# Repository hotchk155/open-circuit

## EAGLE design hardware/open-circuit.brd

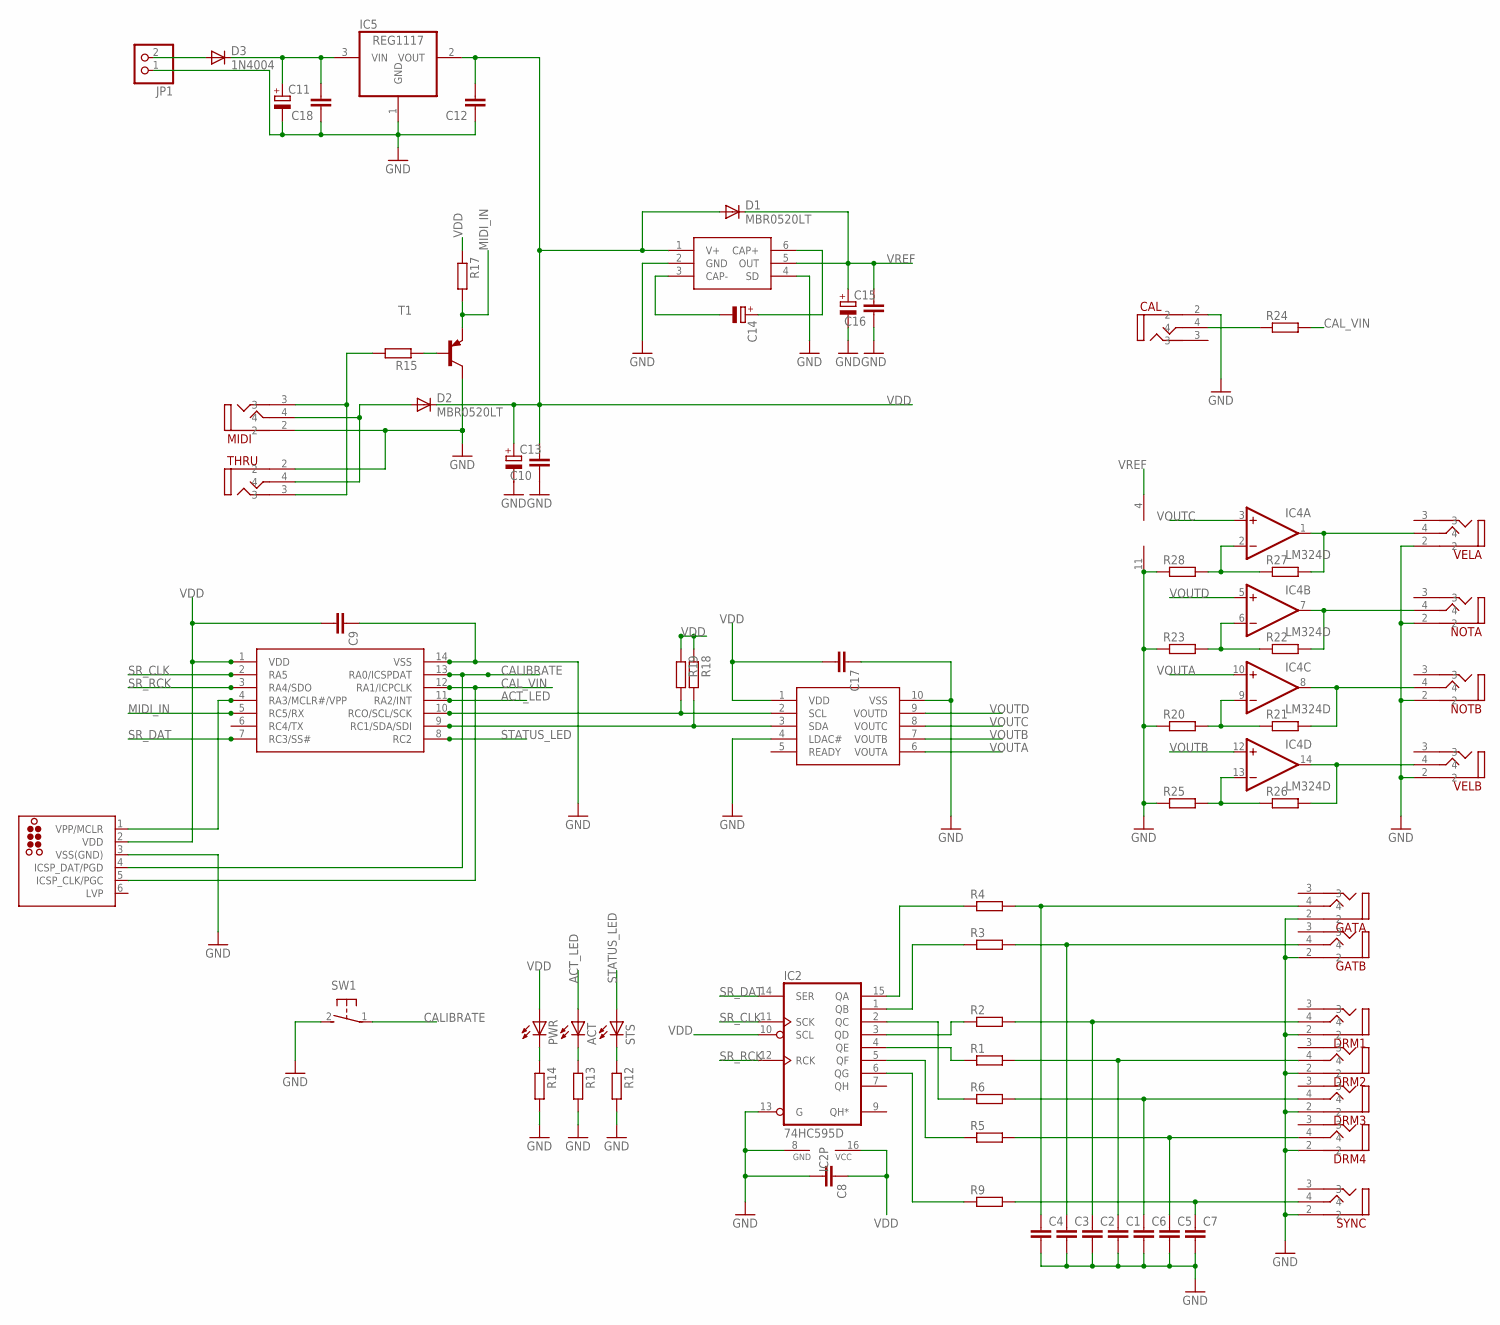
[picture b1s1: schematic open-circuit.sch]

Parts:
ACT: LED3MM
C1, C2, C3, C4, C5, C6, C7, C8, C9, C10, C12, C16, C17, C18: C-EUC0805; C0805
C11: CPOL-EUE2.5-5; E2,5-5
C13, C14, C15: CPOL-EUSMCA; SMC_A
CAL: VERTICAL_3_5MM_SOCKET
D1, D2: MBR0520LT; SOD123
D3: 1N4004; DO-VERT
DRM1, DRM2, DRM3, DRM4: VERTICAL_3_5MM_SOCKET
GATA: VERTICAL_3_5MM_SOCKET
GATB: VERTICAL_3_5MM_SOCKET
IC1: PIC16F1825SO14; SO14
IC2: 74HC595D; SO16
IC3: MCP4728_QUAD_DAC; MSOP10
IC4: LM324D; SO14
IC5: REG1117; SOT223
IC6: LM27675M5_CHARGEPUMP; SOT23-6
ISCP: TC2030-MCP-NL
JP1: PINHD-1X2; 1X02
MIDI: VERTICAL_3_5MM_SOCKET
NOTA: VERTICAL_3_5MM_SOCKET
NOTB: VERTICAL_3_5MM_SOCKET
PWR: LED3MM
R1, R2, R3, R4, R5, R6, R9, R12, R13, R14, R15, R17, R18, R19, R20, R21, R22, R23, R24, R25, R26, R27, R28: R-EU_R0805; R0805
STS: LED3MM
SW1: 31-XX; B3F-31XX
SYNC: VERTICAL_3_5MM_SOCKET
T1: MMBT3906LT1-PNP-SOT23-BEC; SOT23-BEC
THRU: VERTICAL_3_5MM_SOCKET
VELA: VERTICAL_3_5MM_SOCKET
VELB: VERTICAL_3_5MM_SOCKET

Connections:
ACT_LED: ACT.A, IC1.11 (RA2/INT)
CALIBRATE: IC1.13 (RA0/ICSPDAT), ISCP.4 (ICSP_DAT/PGD), SW1.1
CAL_VIN: IC1.12 (RA1/ICPCLK), ISCP.5 (ICSP_CLK/PGC), R24.2
GND: C1.2, C2.2, C3.2, C4.2, C5.2, C6.2, C7.2, C8.2, C9.1, C10.1, C11.-, C12.1, C13.-, C15.-, C16.1, C17.1, C18.1, CAL.2, DRM1.2, DRM2.2, DRM3.2, DRM4.2, GATA.2, GATB.2, IC1.14 (VSS), IC2.8 (GND), IC2.13 (G), IC3.4 (LDAC#), IC3.10 (VSS), IC4.11 (V-), IC5.1 (GND), IC6.2 (GND), IC6.4 (SD), ISCP.3 (VSS(GND)), JP1.1, MIDI.2, NOTA.2, NOTB.2, R12.2, R13.2, R14.2, R20.1, R23.1, R25.1, R28.1, SW1.2 (S), SYNC.2, T1.C, THRU.2, VELA.2, VELB.2
MIDI_IN: IC1.5 (RC5/RX), R17.2, T1.E
unnamed: C4.1, GATA.4, R4.2
unnamed: IC4.1 (OUT), R27.2, VELA.4
unnamed: IC4.7 (OUT), NOTA.4, R22.2
unnamed: IC4.8 (OUT), NOTB.4, R21.2
unnamed: IC4.14 (OUT), R26.2, VELB.4
unnamed: C3.1, GATB.4, R3.2
unnamed: C2.1, DRM1.4, R2.2
unnamed: C1.1, DRM2.4, R1.2
unnamed: C6.1, DRM3.4, R6.2
unnamed: C5.1, DRM4.4, R5.2
unnamed: C7.1, R9.2, SYNC.4
unnamed: IC2.15 (QA), R4.1
unnamed: IC2.1 (QB), R3.1
unnamed: R15.1, T1.B
unnamed: IC2.4 (QE), R1.1
unnamed: IC2.3 (QD), R2.1
unnamed: IC2.5 (QF), R5.1
unnamed: IC2.6 (QG), R9.1
unnamed: C11.+, C18.2, D3.C, IC5.3 (VIN)
unnamed: MIDI.3, R15.2, THRU.3
unnamed: IC1.10 (RCO/SCL/SCK), IC3.2 (SCL), R19.2
unnamed: IC1.9 (RC1/SDA/SDI), IC3.3 (SDA), R18.2
unnamed: C14.-, IC6.3 (CAP-)
unnamed: C14.+, IC6.6 (CAP+)
unnamed: IC4.2 (-IN), R27.1, R28.2
unnamed: IC4.6 (-IN), R22.1, R23.2
unnamed: IC4.9 (-IN), R20.2, R21.1
unnamed: IC4.13 (-IN), R25.2, R26.1
unnamed: CAL.4, R24.1
unnamed: IC1.4 (RA3/MCLR#/VPP), ISCP.1 (VPP/MCLR)
unnamed: PWR.K (C), R14.1
unnamed: ACT.K (C), R13.1
unnamed: R12.1, STS.K (C)
unnamed: IC2.2 (QC), R6.1
unnamed: D2.A, MIDI.4, THRU.4
unnamed: D3.A, JP1.2
SR_CLK: IC1.2 (RA5), IC2.11 (SCK)
SR_DAT: IC1.7 (RC3/SS#), IC2.14 (SER)
SR_RCK: IC1.3 (RA4/SDO), IC2.12 (RCK)
STATUS_LED: IC1.8 (RC2), STS.A
VDD: C8.1, C9.2, C10.2, C12.2, C13.+, C17.2, D1.A, D2.C, IC1.1 (VDD), IC2.10 (SCL), IC2.16 (VCC), IC3.1 (VDD), IC5.2 (VOUT), IC6.1 (V+), ISCP.2 (VDD), PWR.A, R17.1, R18.1, R19.1
VOUTA: IC3.6 (VOUTA), IC4.10 (+IN)
VOUTB: IC3.7 (VOUTB), IC4.12 (+IN)
VOUTC: IC3.8 (VOUTC), IC4.3 (+IN)
VOUTD: IC3.9 (VOUTD), IC4.5 (+IN)
VREF: C15.+, C16.2, D1.C, IC4.4 (V+), IC6.5 (OUT)

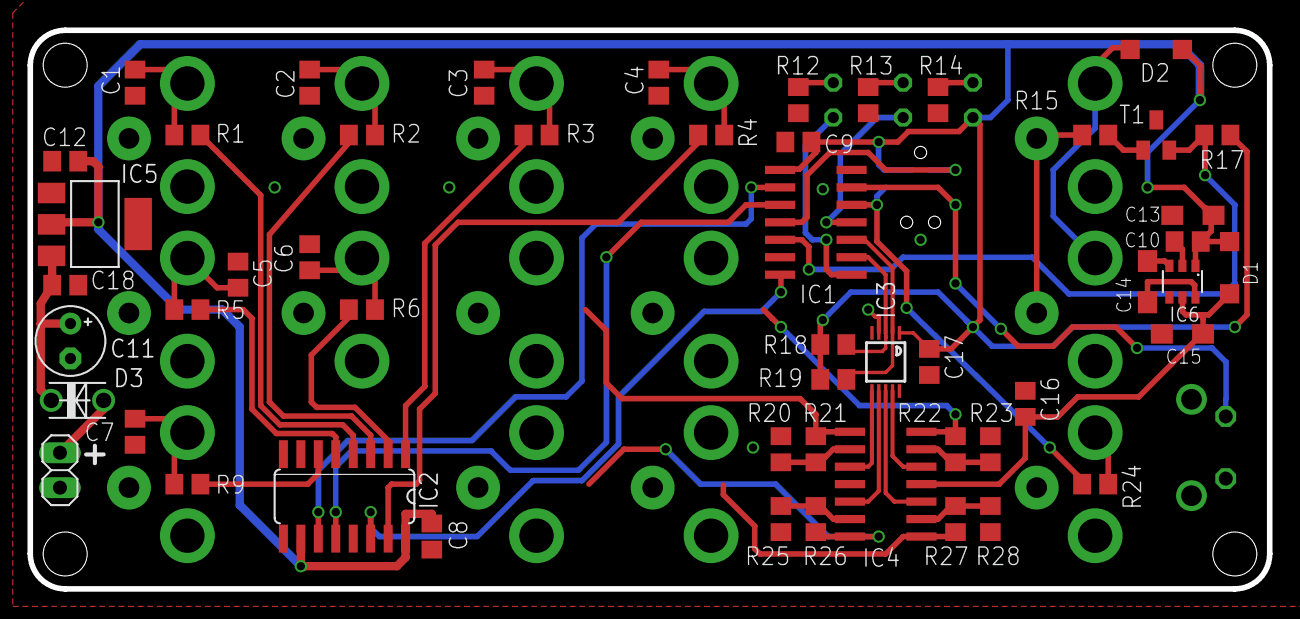
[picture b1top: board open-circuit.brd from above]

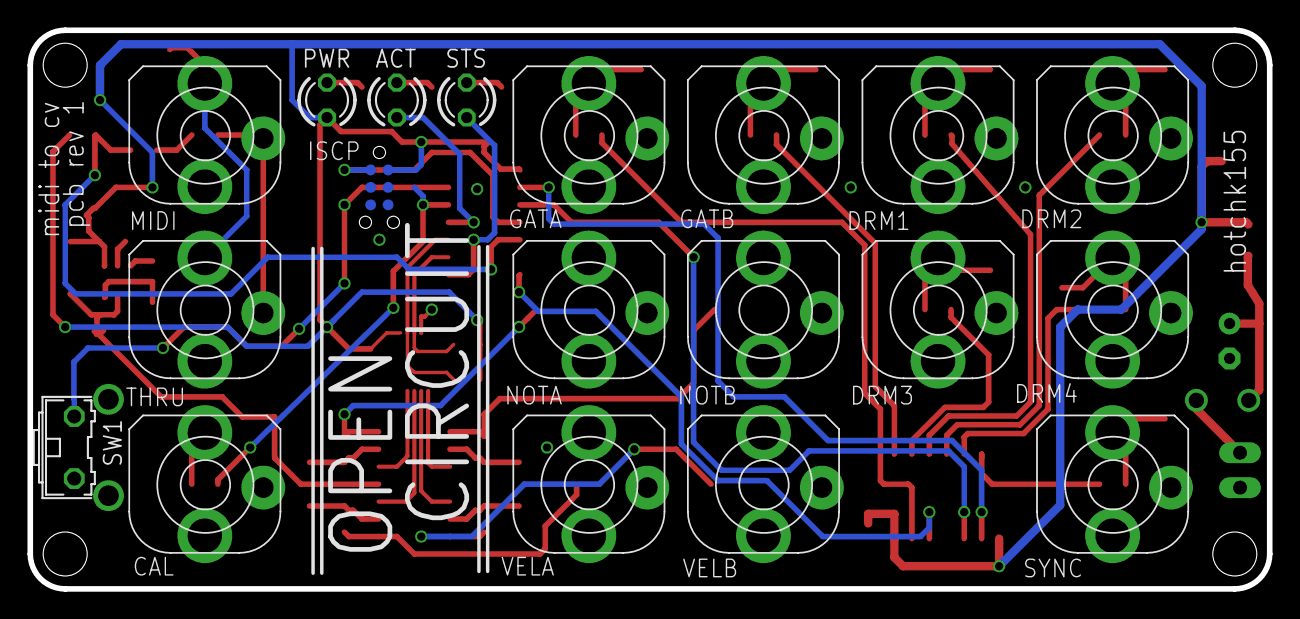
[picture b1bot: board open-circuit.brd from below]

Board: 2 copper layers, 90.2 x 40.6 mm, 71 parts (19 on the bottom side), 51 nets.

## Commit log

2015-11-22 midi cv
2015-11-23 fix input transistor
2015-11-24 i2c experiments
2015-11-24 comparator stuff
2015-11-24 add 5V voltage reg
2015-11-24 change schottky footprint
2015-12-10 initial test of pcb
2015-12-10 stuff

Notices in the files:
parts and their libraries:
tag-connect: ©2009 ROFA.cz - modified and updated by Robert Darlington ‹rdarlington@gmail.com›
